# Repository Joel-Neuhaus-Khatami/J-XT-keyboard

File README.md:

# XT Keyboard Project

NOTE: The RP2040 based design is being replaced with an STM32 variety instead. The readme is thus out of date, however the case files are final
New pcb and firmware will be merged soon.

This repo is for all the files used in designing and manufacturing a mechanical keyboard that I made from scratch.
The keyboard itself is a modified XT layout, which was a very popular layout for 1980's keyboards.

The case is inspired by the IBM Model F77, Cherry G80-0418 and the modern NCR80.
Later angularity and side-bezel thickness was inspired by the Pravetz 16 from the Soviet Union and various NCR G80 varieties, for example the NCR G80-0478.

The PCB is designed Cherry style switch sockets meant for soldering,  all of which are south facing to avoid Cherry profile interference.
The layout is a mix of various layout types, such as the ISO left side 1.25u shift, split right shift, split backspace, which are not changeable.
It does however support stepped caps lock as well as a regular caps lock.
The final PCB iteration is designed with an STM32 chip and currently has only QMK firmware compatibility. This design is confirmed working (from the fact that this README is currently being authored with it).
The PCB was originally designed with using the ATMega32u4 first, then the RP2040, however none of these worked and should be discarded if found in the git history.
Due to the case dimensions, the main intended I/O for the keyboard is a 4-pin Molex Pico EZmate connector and a daughterboard,
in this instance the UDB (Unified Daughterboard) C4. For previous iterations, a full USB type C recepticle + ESD protection diode was added, but these were removed to reduce complexity and assembly time.

## 1. Layout

The layout is a mix of the standard HHKB for the Alphanumerical section, XT-esque left side F-row and a 3x5 1U grid inspired by the IBM Model F-77
  
## 2. Schematics

Early visualization of switch matrix (This layout was changed tremendously due to later solutions for multiple layouts)

Switch matrix translated to Kicad schematics

Full schematics of the board

Routed pcb

3D render (front)

3D render (back)

RP2040, Crystal and Debug pins

USB Type C Recepticle, ESD Protection Diode and 4-pin Molex Connector

## 3. Case

Top case w/ plate

Top and Bottom case side profile

Back view including slit for UDB implementation

Inside view of Top case, showing plate top mount + UDB implementation

Inside view of Bottom case

Bottom

## 4. Acknowledgements on PCB design

Given that this project is open source, the shortcomings of the designs and reflections should be acknowledged as its own separate section. The main issue design wise with the PCB is the the 100nF capacitor being on the top rather than the bottom of the PCB. There is no doubt that the capacitor needed to be much closer to RST, however it could have been implemented more elegantly, but this wasn't possible due to time constraints. Also, the board has little/no indicators or tools to perform debugging other than the available BOOT and RST buttons on the back. Indicator lights and available pins for the purposes of debugging would have been useful, and could present a very challenging debugging experience.

To be posted:
Manufactured PCBA and Aluminium case

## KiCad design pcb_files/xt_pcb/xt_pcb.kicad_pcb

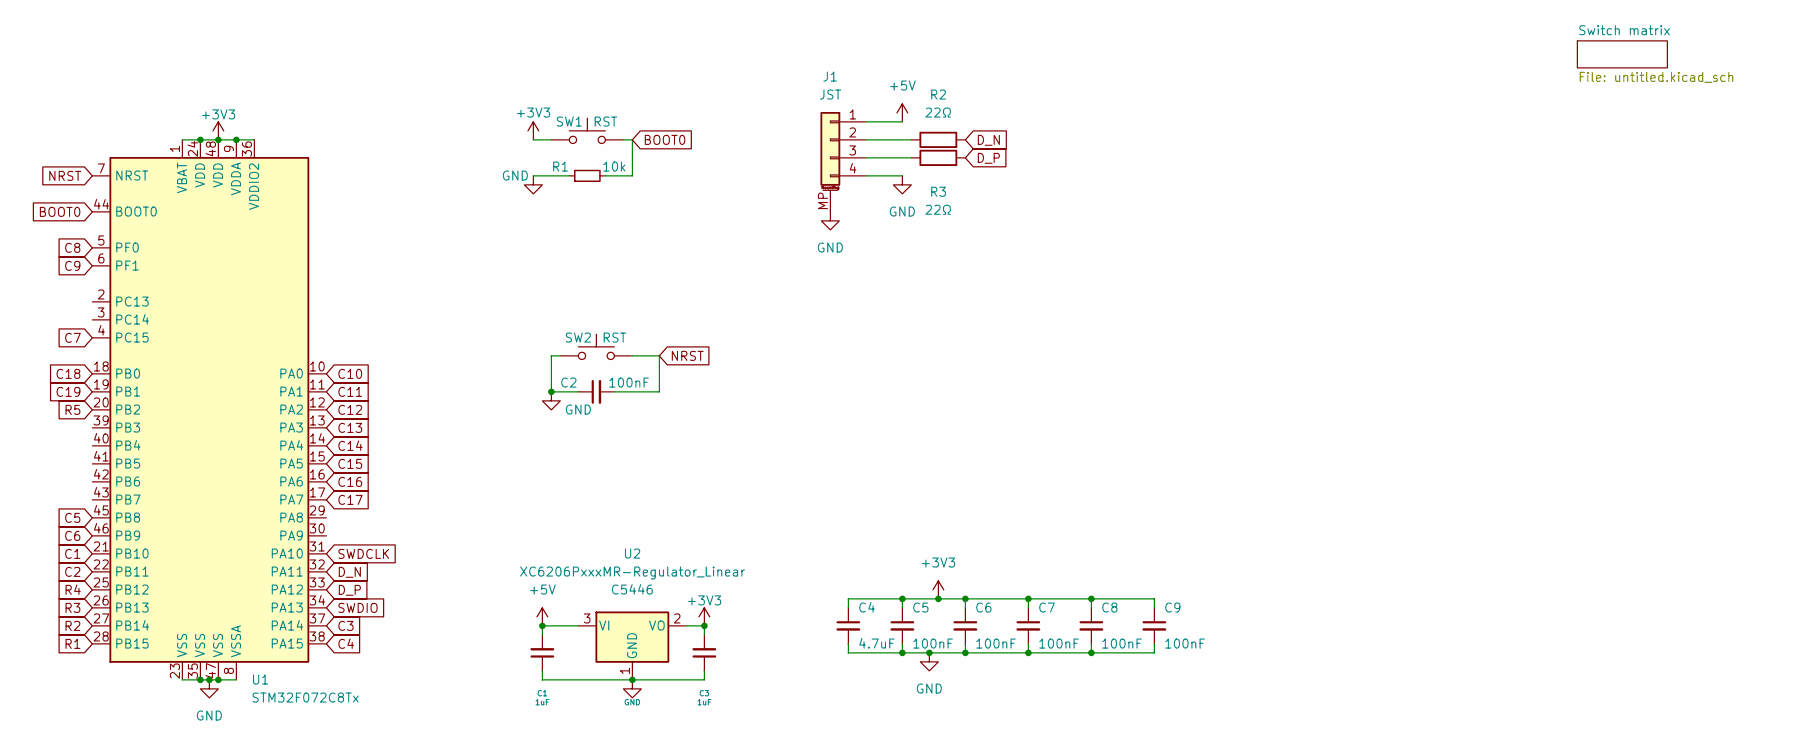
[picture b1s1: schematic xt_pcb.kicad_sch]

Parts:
C1, C3: 1uF; C_0402_1005Metric; LCSC C52923
C2: 100nF; C_0603_1608Metric_Pad1.08x0.95mm_HandSolder; LCSC C307331
C4: 4.7uF; C_0402_1005Metric; LCSC C23733
C5, C6, C7, C8, C9: 100nF; C_0402_1005Metric; LCSC C307331
J1: JST; Molex_Pico-EZmate_78171-0004_1x04-1MP_P1.20mm_Vertical; LCSC C588524
R1: 10k; R_0402_1005Metric; LCSC C25744
R2, R3: 22Ω; C_0402_1005Metric; LCSC C25092
SW1, SW2: RST; SW_SPST_SKQG_WithoutStem; LCSC C139779
U1: STM32F072C8Tx; LQFP-48_7x7mm_P0.5mm; LCSC C80488
U2: XC6206PxxxMR-Regulator_Linear; SOT-23; LCSC C5446

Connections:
+3V3: C3.2, C4.1, C5.1, C6.1, C7.1, C8.1, C9.1, SW1.1, U1.1 (VBAT), U1.9 (VDDA), U1.24 (VDD), U1.36 (VDDIO2), U1.48 (VDD), U2.2 (VO)
+5V: C1.2, J1.1, U2.3 (VI)
BOOT0: R1.2, SW1.2, U1.44 (BOOT0)
C1: U1.21 (PB10); also elsewhere on the board
C2: U1.22 (PB11); also elsewhere on the board
C3: U1.37 (PA14); also elsewhere on the board
C4: U1.38 (PA15); also elsewhere on the board
C5: U1.45 (PB8); also elsewhere on the board
C6: U1.46 (PB9); also elsewhere on the board
C7: U1.4 (PC15); also elsewhere on the board
C8: U1.5 (PF0); also elsewhere on the board
C9: U1.6 (PF1); also elsewhere on the board
C10: U1.10 (PA0); also elsewhere on the board
C11: U1.11 (PA1); also elsewhere on the board
C12: U1.12 (PA2); also elsewhere on the board
C13: U1.13 (PA3); also elsewhere on the board
C14: U1.14 (PA4); also elsewhere on the board
C15: U1.15 (PA5); also elsewhere on the board
C16: U1.16 (PA6); also elsewhere on the board
C17: U1.17 (PA7); also elsewhere on the board
C18: U1.18 (PB0); also elsewhere on the board
C19: U1.19 (PB1); also elsewhere on the board
D_N: R2.2, U1.32 (PA11)
D_P: R3.2, U1.33 (PA12)
GND: C1.1, C2.1, C3.1, C4.2, C5.2, C6.2, C7.2, C8.2, C9.2, J1.4, J1.MP (MountPin), R1.1, SW2.1, U1.8 (VSSA), U1.23 (VSS), U1.35 (VSS), U1.47 (VSS), U2.1 (GND)
NRST: C2.2, SW2.2, U1.7 (NRST)
unnamed: J1.2, R2.1
unnamed: J1.3, R3.1
R1: U1.28 (PB15); also elsewhere on the board
R2: U1.27 (PB14); also elsewhere on the board
R3: U1.26 (PB13); also elsewhere on the board
R4: U1.25 (PB12); also elsewhere on the board
R5: U1.20 (PB2); also elsewhere on the board
SWDCLK: U1.31 (PA10)
SWDIO: U1.34 (PA13)

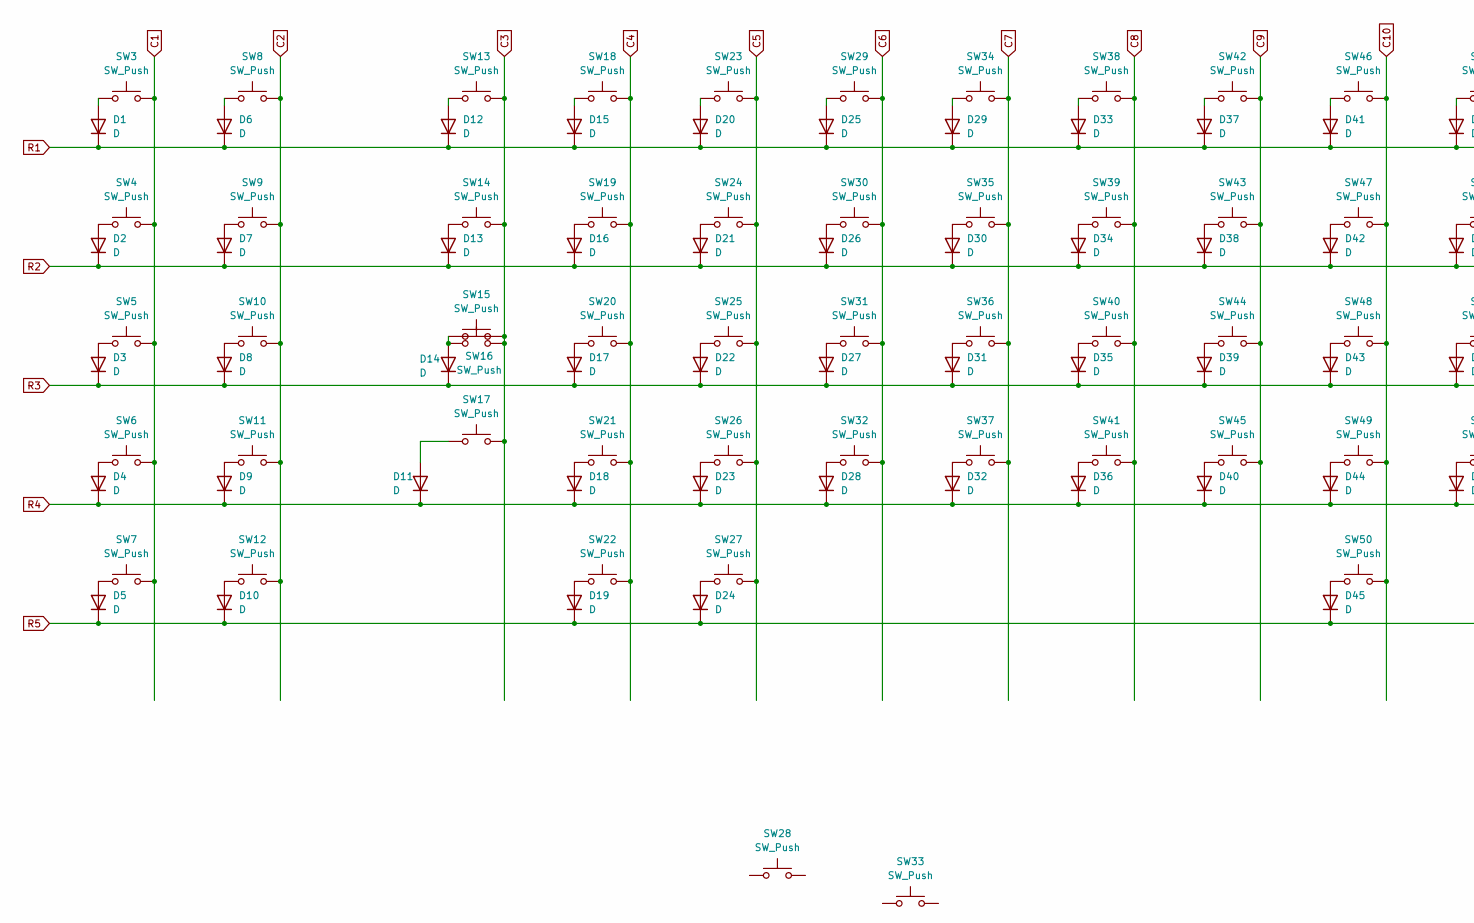
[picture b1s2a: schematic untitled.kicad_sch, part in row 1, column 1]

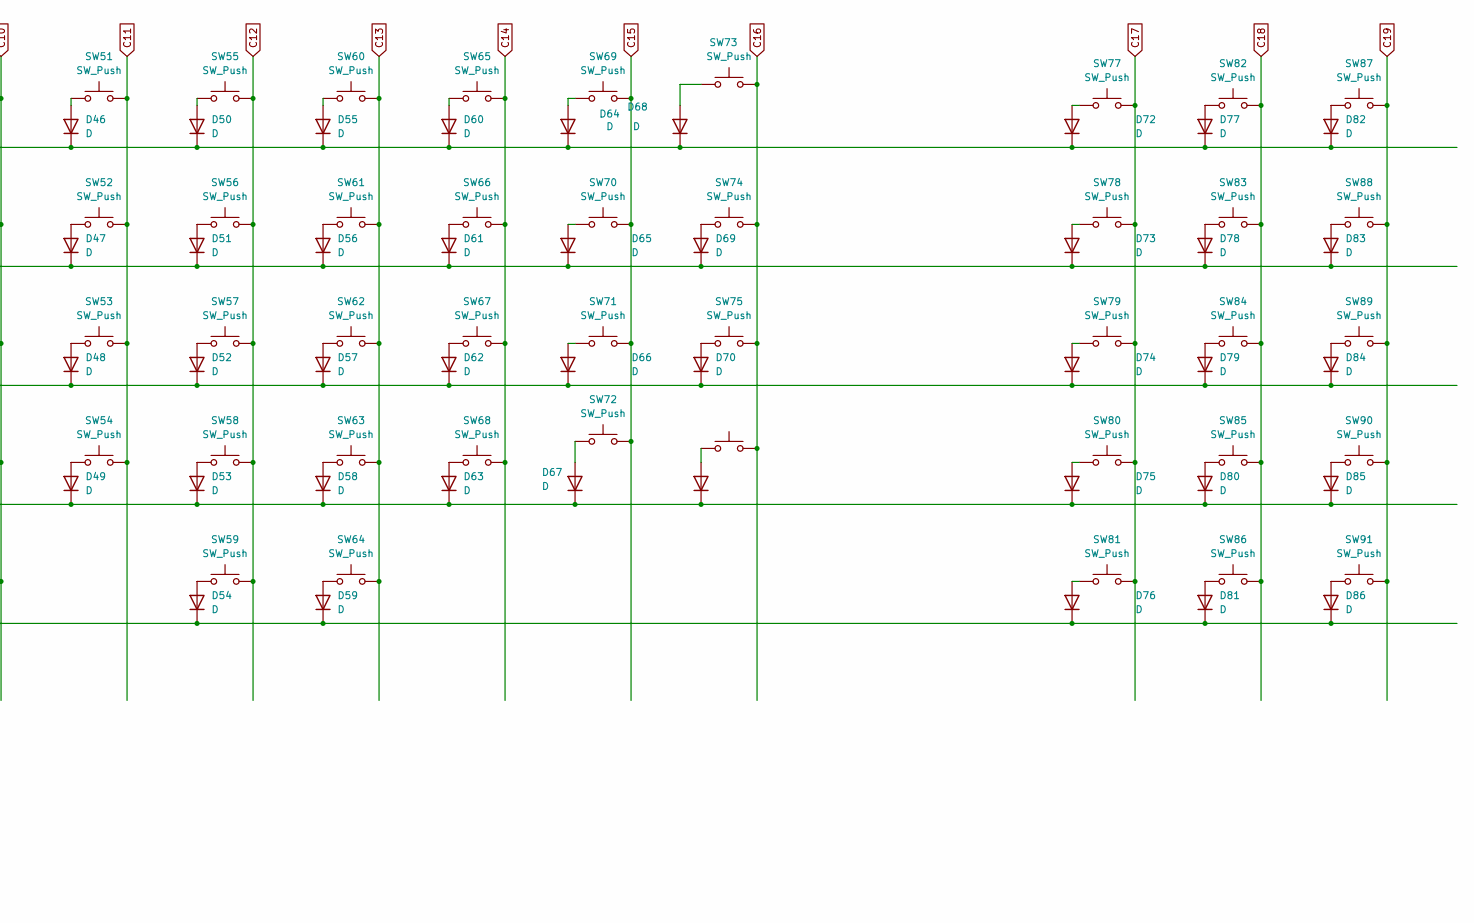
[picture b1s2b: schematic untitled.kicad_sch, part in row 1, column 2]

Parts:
D1, D2, D3, D4, D5, D6, D7, D8, D9, D10, D11, D12, D13, D14, D15, D16, D17, D18, D19, D20, D21, D22, D23, D24, D25, D26, D27, D28, D29, D30, D31, D32, D33, D34, D35, D36, D37, D38, D39, D40, D41, D42, D43, D44, D45, D46, D47, D48, D49, D50, D51, D52, D53, D54, D55, D56, D57, D58, D59, D60, D61, D62, D63, D64, D65, D66, D67, D68, D69, D70, D71, D72, D73, D74, D75, D76, D77, D78, D79, D80, D81, D82, D83, D84, D85, D86: D; D_SOD-123
SW3, SW4, SW5, SW6, SW7, SW8, SW9, SW10, SW11, SW12, SW13, SW18, SW19, SW20, SW21, SW22, SW23, SW24, SW25, SW26, SW29, SW30, SW31, SW32, SW34, SW35, SW36, SW37, SW38, SW39, SW40, SW41, SW42, SW43, SW44, SW45, SW46, SW47, SW48, SW49, SW51, SW52, SW53, SW54, SW55, SW56, SW57, SW58, SW60, SW61, SW62, SW63, SW64, SW65, SW66, SW67, SW68, SW69, SW70, SW71, SW73, SW76, SW77, SW78, SW79, SW80, SW81, SW82, SW83, SW84, SW85, SW86, SW87, SW88, SW89, SW90, SW91: SW_Push; SW_Cherry_MX_PCB_1.00u
SW14, SW74: SW_Push; SW_Cherry_MX_PCB_1.50u
SW15: SW_Push; SW_Cherry_MX_PCB_1.75u
SW16, SW17, SW27, SW59: SW_Push; SW_Cherry_MX_PCB_1.25u
SW28: SW_Push; Stabilizer_Cherry_MX_2.00u
SW33: SW_Push; Stabilizer_Cherry_MX_6.25u
SW50: SW_Push; SW_Cherry_MX_PCB_6.25u
SW72: SW_Push; SW_Cherry_MX_Plate_1.75u
SW75: SW_Push; SW_Cherry_MX_PCB_2.25u

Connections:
C1: SW3.2, SW4.2, SW5.2, SW6.2, SW7.2; also elsewhere on the board
C2: SW8.2, SW9.2, SW10.2, SW11.2, SW12.2; also elsewhere on the board
C3: SW13.2, SW14.2, SW15.2, SW16.2, SW17.2; also elsewhere on the board
C4: SW18.2, SW19.2, SW20.2, SW21.2, SW22.2; also elsewhere on the board
C5: SW23.2, SW24.2, SW25.2, SW26.2, SW27.2; also elsewhere on the board
C6: SW29.2, SW30.2, SW31.2, SW32.2; also elsewhere on the board
C7: SW34.2, SW35.2, SW36.2, SW37.2; also elsewhere on the board
C8: SW38.2, SW39.2, SW40.2, SW41.2; also elsewhere on the board
C9: SW42.2, SW43.2, SW44.2, SW45.2; also elsewhere on the board
C10: SW46.2, SW47.2, SW48.2, SW49.2, SW50.2; also elsewhere on the board
C11: SW51.2, SW52.2, SW53.2, SW54.2; also elsewhere on the board
C12: SW55.2, SW56.2, SW57.2, SW58.2, SW59.2; also elsewhere on the board
C13: SW60.2, SW61.2, SW62.2, SW63.2, SW64.2; also elsewhere on the board
C14: SW65.2, SW66.2, SW67.2, SW68.2; also elsewhere on the board
C15: SW69.2, SW70.2, SW71.2, SW72.2; also elsewhere on the board
C16: SW73.2, SW74.2, SW75.2, SW76.2; also elsewhere on the board
C17: SW77.2, SW78.2, SW79.2, SW80.2, SW81.2; also elsewhere on the board
C18: SW82.2, SW83.2, SW84.2, SW85.2, SW86.2; also elsewhere on the board
C19: SW87.2, SW88.2, SW89.2, SW90.2, SW91.2; also elsewhere on the board
unnamed: D1.2 (A), SW3.1
unnamed: D2.2 (A), SW4.1
unnamed: D3.2 (A), SW5.1
unnamed: D4.2 (A), SW6.1
unnamed: D5.2 (A), SW7.1
unnamed: D6.2 (A), SW8.1
unnamed: D7.2 (A), SW9.1
unnamed: D8.2 (A), SW10.1
unnamed: D9.2 (A), SW11.1
unnamed: D10.2 (A), SW12.1
unnamed: D11.2 (A), SW17.1
unnamed: D12.2 (A), SW13.1
unnamed: D13.2 (A), SW14.1
unnamed: D14.2 (A), SW15.1, SW16.1
unnamed: D15.2 (A), SW18.1
unnamed: D16.2 (A), SW19.1
unnamed: D17.2 (A), SW20.1
unnamed: D18.2 (A), SW21.1
unnamed: D19.2 (A), SW22.1
unnamed: D20.2 (A), SW23.1
unnamed: D21.2 (A), SW24.1
unnamed: D22.2 (A), SW25.1
unnamed: D23.2 (A), SW26.1
unnamed: D24.2 (A), SW27.1
unnamed: D25.2 (A), SW29.1
unnamed: D26.2 (A), SW30.1
unnamed: D27.2 (A), SW31.1
unnamed: D28.2 (A), SW32.1
unnamed: D29.2 (A), SW34.1
unnamed: D30.2 (A), SW35.1
unnamed: D31.2 (A), SW36.1
unnamed: D32.2 (A), SW37.1
unnamed: D33.2 (A), SW38.1
unnamed: D34.2 (A), SW39.1
unnamed: D35.2 (A), SW40.1
unnamed: D36.2 (A), SW41.1
unnamed: D37.2 (A), SW42.1
unnamed: D38.2 (A), SW43.1
unnamed: D39.2 (A), SW44.1
unnamed: D40.2 (A), SW45.1
unnamed: D41.2 (A), SW46.1
unnamed: D42.2 (A), SW47.1
unnamed: D43.2 (A), SW48.1
unnamed: D44.2 (A), SW49.1
unnamed: D45.2 (A), SW50.1
unnamed: D46.2 (A), SW51.1
unnamed: D47.2 (A), SW52.1
unnamed: D48.2 (A), SW53.1
unnamed: D49.2 (A), SW54.1
unnamed: D50.2 (A), SW55.1
unnamed: D51.2 (A), SW56.1
unnamed: D52.2 (A), SW57.1
unnamed: D53.2 (A), SW58.1
unnamed: D54.2 (A), SW59.1
unnamed: D55.2 (A), SW60.1
unnamed: D56.2 (A), SW61.1
unnamed: D57.2 (A), SW62.1
unnamed: D58.2 (A), SW63.1
unnamed: D59.2 (A), SW64.1
unnamed: D60.2 (A), SW65.1
unnamed: D61.2 (A), SW66.1
unnamed: D62.2 (A), SW67.1
unnamed: D63.2 (A), SW68.1
unnamed: D64.2 (A), SW69.1
unnamed: D65.2 (A), SW70.1
unnamed: D66.2 (A), SW71.1
unnamed: D67.2 (A), SW72.1
unnamed: D68.2 (A), SW73.1
unnamed: D69.2 (A), SW74.1
unnamed: D70.2 (A), SW75.1
unnamed: D71.2 (A), SW76.1
unnamed: D72.2 (A), SW77.1
unnamed: D73.2 (A), SW78.1
unnamed: D74.2 (A), SW79.1
unnamed: D75.2 (A), SW80.1
unnamed: D76.2 (A), SW81.1
unnamed: D77.2 (A), SW82.1
unnamed: D78.2 (A), SW83.1
unnamed: D79.2 (A), SW84.1
unnamed: D80.2 (A), SW85.1
unnamed: D81.2 (A), SW86.1
unnamed: D82.2 (A), SW87.1
unnamed: D83.2 (A), SW88.1
unnamed: D84.2 (A), SW89.1
unnamed: D85.2 (A), SW90.1
unnamed: D86.2 (A), SW91.1
R1: D1.1 (K), D6.1 (K), D12.1 (K), D15.1 (K), D20.1 (K), D25.1 (K), D29.1 (K), D33.1 (K), D37.1 (K), D41.1 (K), D46.1 (K), D50.1 (K), D55.1 (K), D60.1 (K), D64.1 (K), D68.1 (K), D72.1 (K), D77.1 (K), D82.1 (K); also elsewhere on the board
R2: D2.1 (K), D7.1 (K), D13.1 (K), D16.1 (K), D21.1 (K), D26.1 (K), D30.1 (K), D34.1 (K), D38.1 (K), D42.1 (K), D47.1 (K), D51.1 (K), D56.1 (K), D61.1 (K), D65.1 (K), D69.1 (K), D73.1 (K), D78.1 (K), D83.1 (K); also elsewhere on the board
R3: D3.1 (K), D8.1 (K), D14.1 (K), D17.1 (K), D22.1 (K), D27.1 (K), D31.1 (K), D35.1 (K), D39.1 (K), D43.1 (K), D48.1 (K), D52.1 (K), D57.1 (K), D62.1 (K), D66.1 (K), D70.1 (K), D74.1 (K), D79.1 (K), D84.1 (K); also elsewhere on the board
R4: D4.1 (K), D9.1 (K), D11.1 (K), D18.1 (K), D23.1 (K), D28.1 (K), D32.1 (K), D36.1 (K), D40.1 (K), D44.1 (K), D49.1 (K), D53.1 (K), D58.1 (K), D63.1 (K), D67.1 (K), D71.1 (K), D75.1 (K), D80.1 (K), D85.1 (K); also elsewhere on the board
R5: D5.1 (K), D10.1 (K), D19.1 (K), D24.1 (K), D45.1 (K), D54.1 (K), D59.1 (K), D76.1 (K), D81.1 (K), D86.1 (K); also elsewhere on the board

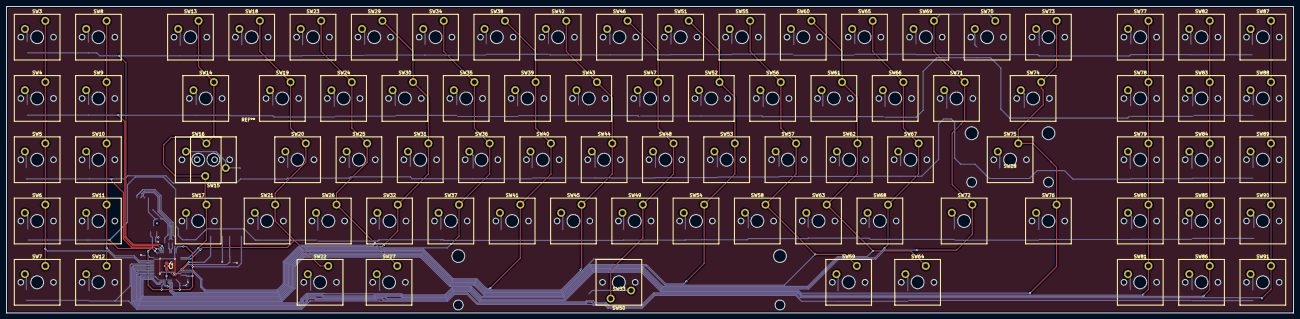
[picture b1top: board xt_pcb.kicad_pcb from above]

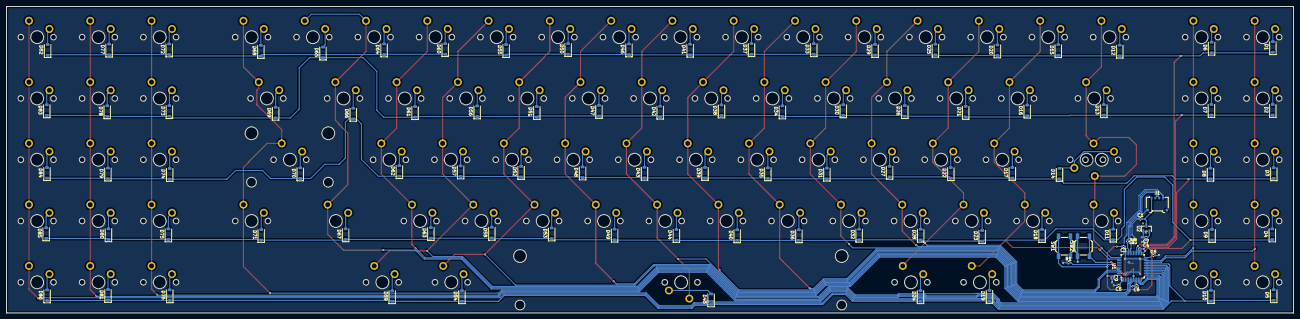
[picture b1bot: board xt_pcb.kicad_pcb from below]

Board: 2 copper layers, 400.1 x 95.2 mm, 192 parts (102 on the bottom side), 119 nets.

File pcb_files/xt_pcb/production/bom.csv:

Designator,Footprint,Quantity,Value,LCSC Part #
"C1, C3",0402,2,1uF,C52923
C2,0603,1,100nF,C307331
C4,0402,1,4.7uF,C23733
"C5, C6, C7, C8, C9",0402,5,100nF,C307331
"D1, D10, D11, D12, D13, D14, D15, D16, D17, D18, D19, D2, D20, D21, D22, D23, D24, D25, D26, D27, D28, D29, D3, D30, D31, D32, D33, D34, D35, D36, D37, D38, D39, D4, D40, D41, D42, D43, D44, D45, D46, D47, D48, D49, D5, D50, D51, D52, D53, D54, D55, D56, D57, D58, D59, D6, D60, D61, D62, D63, D64, D65, D66, D67, D68, D69, D7, D70, D71, D72, D73, D74, D75, D76, D77, D78, D79, D8, D80, D81, D82, D83, D84, D85, D86, D9",D_SOD-123,86,D,
J1,Molex_Pico-EZmate_78171-0004_1x04-1MP_P1.20mm_Vertical,1,JST,C588524
R1,0402,1,10k,C25744
"R2, R3",0402,2,22Ω,C25092
"SW1, SW2",SW_SPST_SKQG_WithoutStem,2,RST,C139779
"SW10, SW11, SW12, SW13, SW18, SW19, SW20, SW21, SW22, SW23, SW24, SW25, SW26, SW29, SW3, SW30, SW31, SW32, SW34, SW35, SW36, SW37, SW38, SW39, SW4, SW40, SW41, SW42, SW43, SW44, SW45, SW46, SW47, SW48, SW49, SW5, SW51, SW52, SW53, SW54, SW55, SW56, SW57, SW58, SW6, SW60, SW61, SW62, SW63, SW64, SW65, SW66, SW67, SW68, SW69, SW7, SW70, SW71, SW73, SW76, SW77, SW78, SW79, SW8, SW80, SW81, SW82, SW83, SW84, SW85, SW86, SW87, SW88, SW89, SW9, SW90, SW91",SW_Cherry_MX_PCB_1.00u,77,SW_Push,
"SW14, SW74",SW_Cherry_MX_PCB_1.50u,2,SW_Push,
SW15,SW_Cherry_MX_PCB_1.75u,1,SW_Push,
"SW16, SW17, SW27, SW59",SW_Cherry_MX_PCB_1.25u,4,SW_Push,
SW28,Stabilizer_Cherry_MX_2.00u,1,SW_Push,
SW33,Stabilizer_Cherry_MX_6.25u,1,SW_Push,
SW50,SW_Cherry_MX_PCB_6.25u,1,SW_Push,
SW72,SW_Cherry_MX_Plate_1.75u,1,SW_Push,
SW75,SW_Cherry_MX_PCB_2.25u,1,SW_Push,
U1,LQFP-48_7x7mm_P0.5mm,1,STM32F072C8Tx,C80488
U2,SOT-23,1,XC6206PxxxMR-Regulator_Linear,C5446

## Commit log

2025-06-03 connected connected the switch matrix to gpio
2025-06-03 tracing adjustments
2025-06-03 drc debugging
2025-06-03 new 5v
2025-06-03 additional 5v + differential adjustments
2025-06-03 tweaks
2025-06-04 prod files
2025-07-23 git test
2025-07-23 deleted file
2025-07-25 routing algorithm used
2025-07-27 routing halluc. removed + usb c added
2025-07-27 esd diode
2025-07-28 debugging + prod files
2025-08-03 rerouting
2025-08-03 removed all 90 deg
2025-08-07 90 deg removed
2025-08-12 vias removed
2025-08-13 cleaned up vias
2025-08-13 new prod files
2025-08-13 removed not needed files
2025-08-13 gerbers + new prod
2025-08-13 (kicad_pcb (version 20241229) (generator "pcbnew") (generator_version "9.0") (layers (0 "F.Cu" signal) (2 "B.Cu" signal) (9 "F.Adhes" user "F.Adhesive") (11 "B.Adhes" user "B.Adhesive") (13 "F.Paste"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
2025-08-13 old files removed
2025-08-14 correct drill files plotted
2025-08-14 gerber zip
2025-08-14 new molex footprint
2025-08-14 rmvd uneeded prod files
2025-08-15 small sch tweaks
2025-08-23 keyboard.json
2025-08-23 firmware tweaks
2025-08-23 pcb tweaks
2025-08-24 firmware + function layering
2025-08-24 bug fixes
2025-08-25 firmware files qmk compiled
2025-09-02 small plate tweal
2025-09-28 fix: removed usb type c
2025-11-28 feat: new stm32 based board in progress
2025-12-20 feat: all mx sockets footprints changed
2025-12-20 feat: added gnd fill
2025-12-21 feat: acheron conncectors for molex added
2025-12-21 feat: new molex connector
2026-01-03 feat: drc fixes
2026-03-29 fixes
2026-04-06 0603 handsolder
2026-04-06 allignment fix
2026-04-06 new footprint
2026-04-17 updated lcsc information
2026-04-17 updated firmware
2026-04-17 updated keymaps
2026-04-17 corrected row keymap
2026-04-20 firmware fixed for actual hardware
2026-04-20 fixed keymaps
2026-04-21 basic md formatting
2026-04-22 Update LICENSE
